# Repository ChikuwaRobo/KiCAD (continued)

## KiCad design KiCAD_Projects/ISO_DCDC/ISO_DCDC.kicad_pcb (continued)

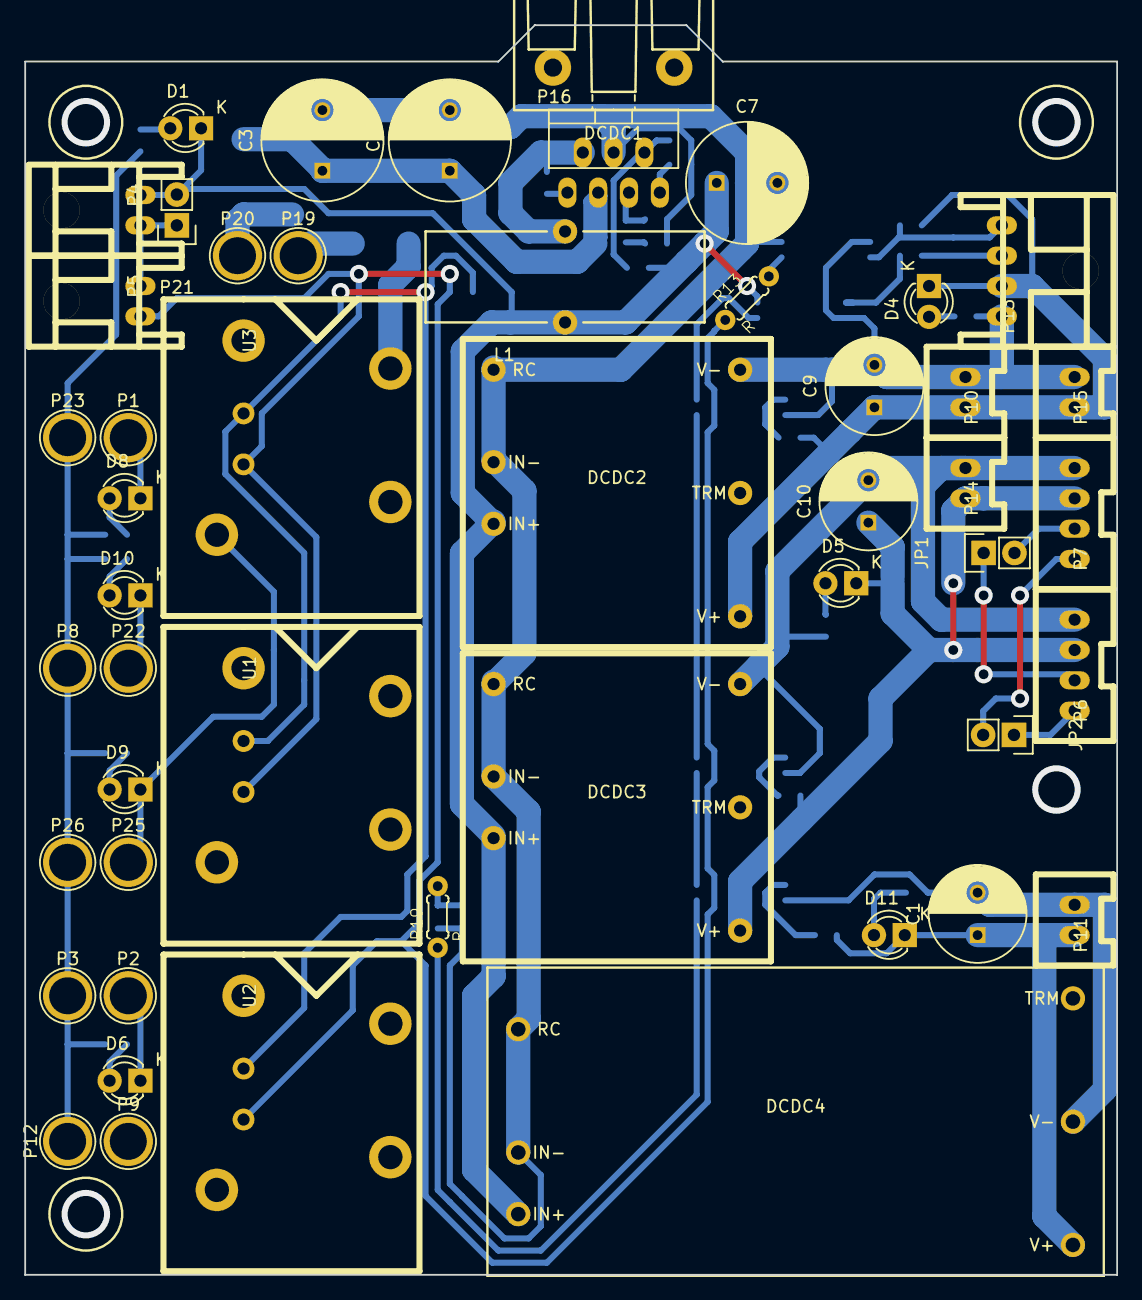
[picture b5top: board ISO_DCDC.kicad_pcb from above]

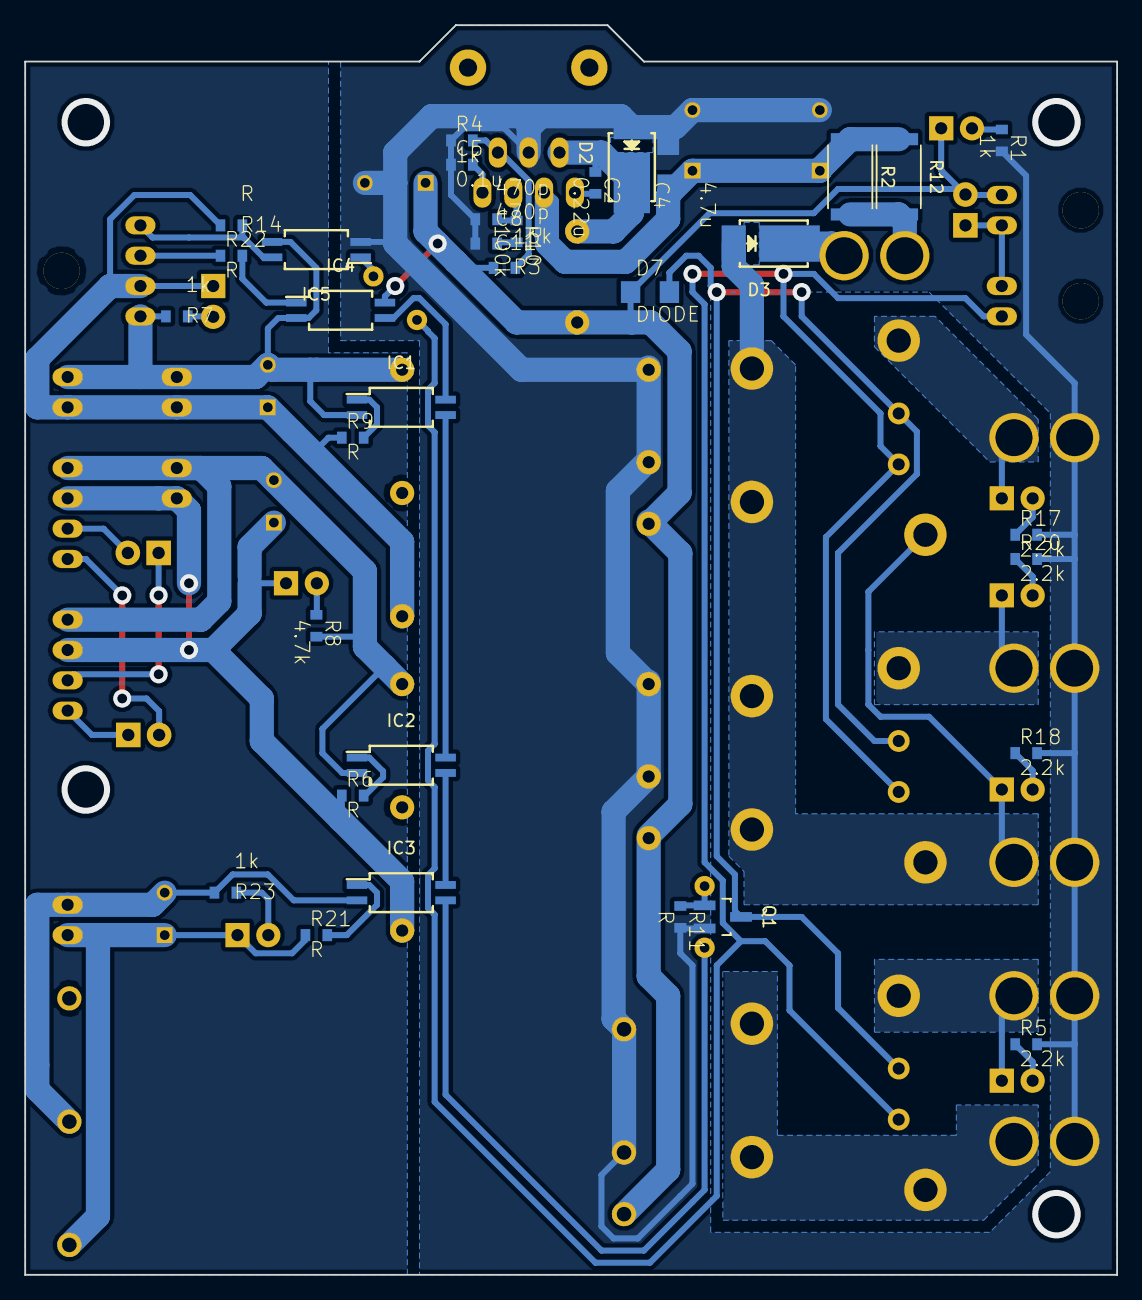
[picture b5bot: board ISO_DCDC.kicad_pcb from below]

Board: 2 copper layers, 90.0 x 103.0 mm, 82 parts (33 on the bottom side), 49 nets.
